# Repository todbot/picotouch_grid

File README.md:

# picotouch_grid

## Demo

https://github.com/user-attachments/assets/54ee2066-7102-474b-aefb-f99e8350b503

another on youtube:  https://www.youtube.com/watch?v=ulmvLfkXsHI

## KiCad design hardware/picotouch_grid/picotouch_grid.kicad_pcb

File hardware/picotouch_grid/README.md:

Uses JLCPCB rules from https://github.com/labtroll/KiCad-DesignRules

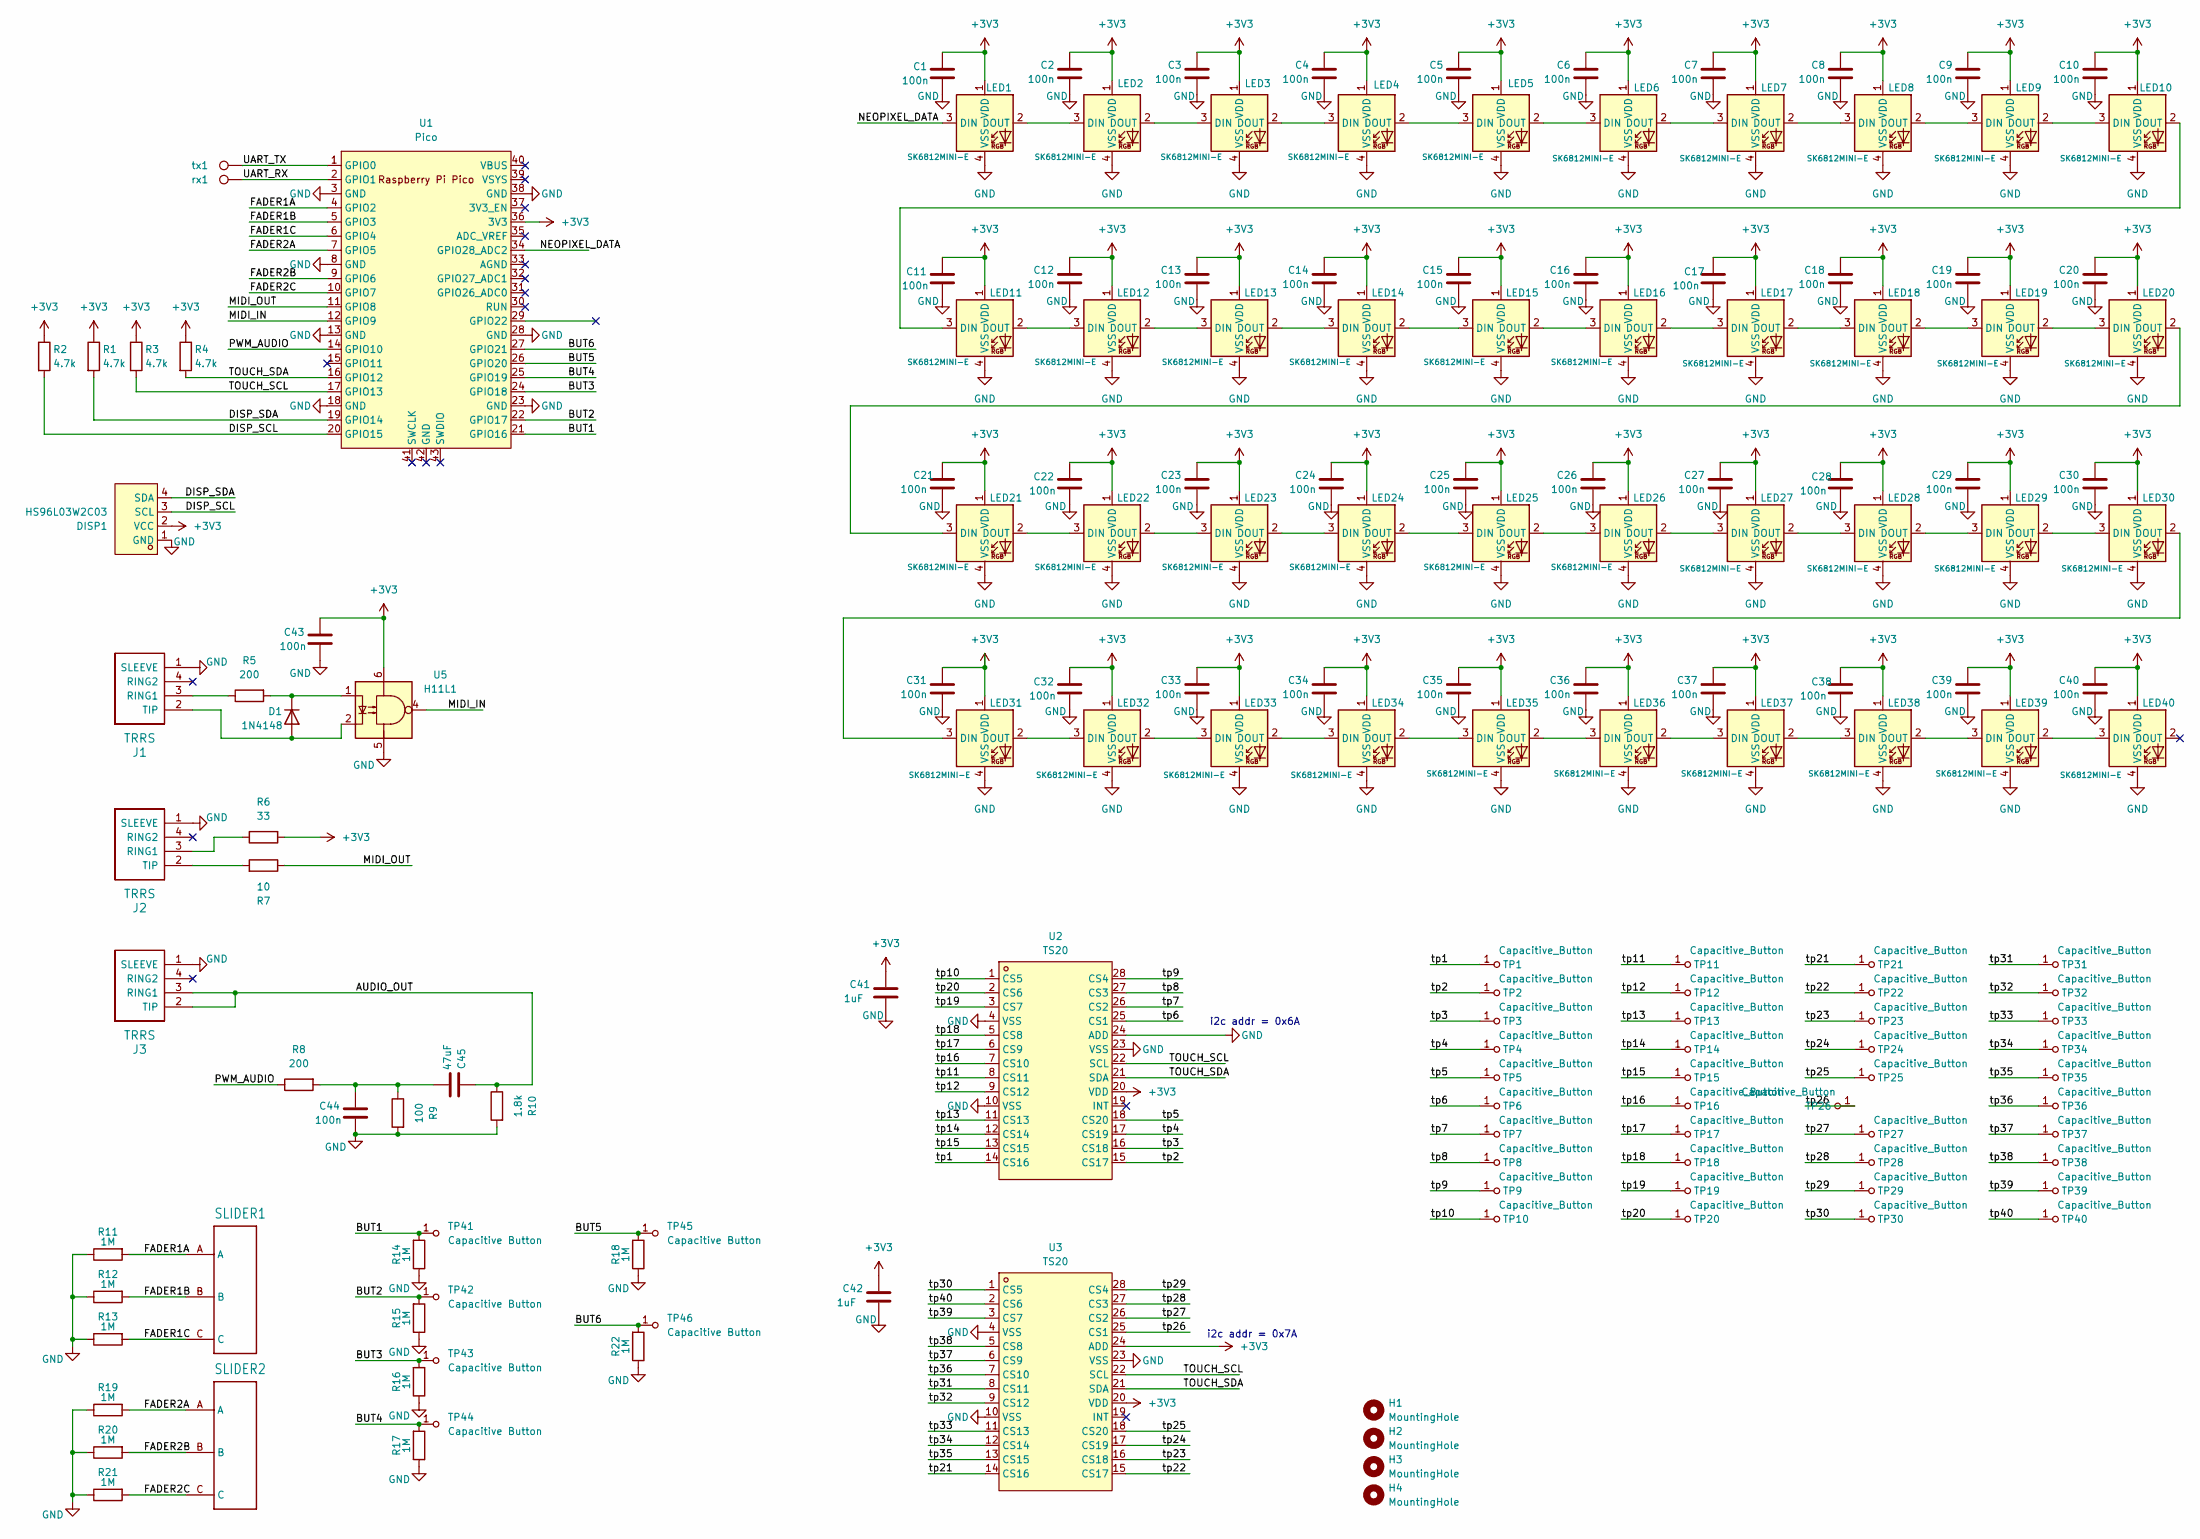
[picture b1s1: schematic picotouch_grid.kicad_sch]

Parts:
C1, C2, C3, C4, C5, C6, C7, C8, C9, C10, C11, C12, C13, C14, C15, C16, C17, C18, C19, C20, C21, C22, C23, C24, C25, C26, C27, C28, C29, C30, C31, C32, C33, C34, C35, C36, C37, C38, C39, C40, C43, C44: 100n; C_0603_1608Metric
C41, C42: 1uF; C_0603_1608Metric
C45: 47uF; C_0603_1608Metric
D1: 1N4148; D_SOD-123
DISP1: HS96L03W2C03; OLED-TH_under_fixed_L27.8-W27.2-P2.54_C9900033791; LCSC Part C5248080
H1, H2, H3, H4: MountingHole; MountingHole_2.7mm_M2.5
J1, J2, J3: TRRS; TRRS-PJ-320D
LED1, LED2, LED3, LED4, LED5, LED6, LED7, LED8, LED9, LED10, LED11, LED12, LED13, LED14, LED15, LED16, LED17, LED18, LED19, LED20, LED21, LED22, LED23, LED24, LED25, LED26, LED27, LED28, LED29, LED30, LED31, LED32, LED33, LED34, LED35, LED36, LED37, LED38, LED39, LED40: SK6812MINI-E; LED_6028R
R1, R2, R3, R4: 4.7k; R_0603_1608Metric
R5, R8: 200; R_0603_1608Metric
R6: 33; R_0603_1608Metric
R7: 10; R_0603_1608Metric
R9: 100; R_0603_1608Metric
R10: 1.8k; R_0603_1608Metric
R11, R12, R13, R14, R15, R16, R17, R18, R19, R20, R21, R22: 1M; R_0603_1608Metric
SLIDER1, SLIDER2: TOUCHSLIDER3_8x40B
TP1, TP2, TP3, TP4, TP5, TP6, TP7, TP8, TP9, TP10, TP11, TP12, TP13, TP14, TP15, TP16, TP17, TP18, TP19, TP20, TP21, TP22, TP23, TP24, TP25, TP26, TP27, TP28, TP29, TP30, TP31, TP32, TP33, TP34, TP35, TP36, TP37, TP38, TP39, TP40: Capacitive_Button; TOUCHPAD_KEY_0.5IN_LEDHOLE
TP41, TP42, TP43, TP44, TP45, TP46: Capacitive Button; Pad-CapacitiveTouch
U1: Pico; RPi_Pico_SMD
U2, U3: TS20; TSSOP-28_L9.7-W4.4-P0.65-LS6.4-BL; LCSC Part C95876
U5: H11L1; DIP-6_W8.89mm_SMDSocket_LongPads
rx1: rx; TestPoint_Pad_D2.0mm
tx1: tx; TestPoint_Pad_D2.0mm

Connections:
+3V3: C1.1, C2.1, C3.1, C4.1, C5.1, C6.1, C7.1, C8.1, C9.1, C10.1, C11.1, C12.1, C13.1, C14.1, C15.1, C16.1, C17.1, C18.1, C19.1, C20.1, C21.1, C22.1, C23.1, C24.1, C25.1, C26.1, C27.1, C28.1, C29.1, C30.1, C31.1, C32.1, C33.1, C34.1, C35.1, C36.1, C37.1, C38.1, C39.1, C40.1, C41.1, C42.1, C43.1, DISP1.2 (VCC), LED1.1 (VDD), LED2.1 (VDD), LED3.1 (VDD), LED4.1 (VDD), LED5.1 (VDD), LED6.1 (VDD), LED7.1 (VDD), LED8.1 (VDD), LED9.1 (VDD), LED10.1 (VDD), LED11.1 (VDD), LED12.1 (VDD), LED13.1 (VDD), LED14.1 (VDD), LED15.1 (VDD), LED16.1 (VDD), LED17.1 (VDD), LED18.1 (VDD), LED19.1 (VDD), LED20.1 (VDD), LED21.1 (VDD), LED22.1 (VDD), LED23.1 (VDD), LED24.1 (VDD), LED25.1 (VDD), LED26.1 (VDD), LED27.1 (VDD), LED28.1 (VDD), LED29.1 (VDD), LED30.1 (VDD), LED31.1 (VDD), LED32.1 (VDD), LED33.1 (VDD), LED34.1 (VDD), LED35.1 (VDD), LED36.1 (VDD), LED37.1 (VDD), LED38.1 (VDD), LED39.1 (VDD), LED40.1 (VDD), R1.1, R2.1, R3.1, R4.1, R6.2, U1.36 (3V3), U2.20 (VDD), U3.20 (VDD), U3.24 (ADD), U5.6
/AUDIO_OUT: C45.1, J3.2 (TIP), J3.3 (RING1), R10.1
/BUT1: R14.2, TP41.1 (A), U1.21 (GPIO16)
/BUT2: R15.2, TP42.1 (A), U1.22 (GPIO17)
/BUT3: R16.2, TP43.1 (A), U1.24 (GPIO18)
/BUT4: R17.2, TP44.1 (A), U1.25 (GPIO19)
/BUT5: R18.2, TP45.1 (A), U1.26 (GPIO20)
/BUT6: R22.2, TP46.1 (A), U1.27 (GPIO21)
/DISP_SCL: DISP1.3 (SCL), R2.2, U1.20 (GPIO15)
/DISP_SDA: DISP1.4 (SDA), R1.2, U1.19 (GPIO14)
/FADER1A: R11.2, SLIDER1.A, U1.4 (GPIO2)
/FADER1B: R12.2, SLIDER1.B, U1.5 (GPIO3)
/FADER1C: R13.2, SLIDER1.C, U1.6 (GPIO4)
/FADER2A: R19.2, SLIDER2.A, U1.7 (GPIO5)
/FADER2B: R20.2, SLIDER2.B, U1.9 (GPIO6)
/FADER2C: R21.2, SLIDER2.C, U1.10 (GPIO7)
/MIDI_IN: U1.12 (GPIO9), U5.4
/MIDI_OUT: R7.1, U1.11 (GPIO8)
/NEOPIXEL_DATA: LED1.3 (DIN), U1.34 (GPIO28_ADC2)
/PWM_AUDIO: R8.1, U1.14 (GPIO10)
/TOUCH_SCL: R3.2, U1.17 (GPIO13), U2.22 (SCL), U3.22 (SCL)
/TOUCH_SDA: R4.2, U1.16 (GPIO12), U2.21 (SDA), U3.21 (SDA)
/UART_RX: U1.2 (GPIO1), rx1.1
/UART_TX: U1.1 (GPIO0), tx1.1
/tp1: TP1.1 (A), U2.14 (CS16)
/tp2: TP2.1 (A), U2.15 (CS17)
/tp3: TP3.1 (A), U2.16 (CS18)
/tp4: TP4.1 (A), U2.17 (CS19)
/tp5: TP5.1 (A), U2.18 (CS20)
/tp6: TP6.1 (A), U2.25 (CS1)
/tp7: TP7.1 (A), U2.26 (CS2)
/tp8: TP8.1 (A), U2.27 (CS3)
/tp9: TP9.1 (A), U2.28 (CS4)
/tp10: TP10.1 (A), U2.1 (CS5)
/tp11: TP11.1 (A), U2.8 (CS11)
/tp12: TP12.1 (A), U2.9 (CS12)
/tp13: TP13.1 (A), U2.11 (CS13)
/tp14: TP14.1 (A), U2.12 (CS14)
/tp15: TP15.1 (A), U2.13 (CS15)
/tp16: TP16.1 (A), U2.7 (CS10)
/tp17: TP17.1 (A), U2.6 (CS9)
/tp18: TP18.1 (A), U2.5 (CS8)
/tp19: TP19.1 (A), U2.3 (CS7)
/tp20: TP20.1 (A), U2.2 (CS6)
/tp21: TP21.1 (A), U3.14 (CS16)
/tp22: TP22.1 (A), U3.15 (CS17)
/tp23: TP23.1 (A), U3.16 (CS18)
/tp24: TP24.1 (A), U3.17 (CS19)
/tp25: TP25.1 (A), U3.18 (CS20)
/tp26: TP26.1 (A), U3.25 (CS1)
/tp27: TP27.1 (A), U3.26 (CS2)
/tp28: TP28.1 (A), U3.27 (CS3)
/tp29: TP29.1 (A), U3.28 (CS4)
/tp30: TP30.1 (A), U3.1 (CS5)
/tp31: TP31.1 (A), U3.8 (CS11)
/tp32: TP32.1 (A), U3.9 (CS12)
/tp33: TP33.1 (A), U3.11 (CS13)
/tp34: TP34.1 (A), U3.12 (CS14)
/tp35: TP35.1 (A), U3.13 (CS15)
/tp36: TP36.1 (A), U3.7 (CS10)
/tp37: TP37.1 (A), U3.6 (CS9)
/tp38: TP38.1 (A), U3.5 (CS8)
/tp39: TP39.1 (A), U3.3 (CS7)
/tp40: TP40.1 (A), U3.2 (CS6)
GND: C1.2, C2.2, C3.2, C4.2, C5.2, C6.2, C7.2, C8.2, C9.2, C10.2, C11.2, C12.2, C13.2, C14.2, C15.2, C16.2, C17.2, C18.2, C19.2, C20.2, C21.2, C22.2, C23.2, C24.2, C25.2, C26.2, C27.2, C28.2, C29.2, C30.2, C31.2, C32.2, C33.2, C34.2, C35.2, C36.2, C37.2, C38.2, C39.2, C40.2, C41.2, C42.2, C43.2, C44.2, DISP1.1 (GND), J1.1 (SLEEVE), J2.1 (SLEEVE), J3.1 (SLEEVE), LED1.4 (VSS), LED2.4 (VSS), LED3.4 (VSS), LED4.4 (VSS), LED5.4 (VSS), LED6.4 (VSS), LED7.4 (VSS), LED8.4 (VSS), LED9.4 (VSS), LED10.4 (VSS), LED11.4 (VSS), LED12.4 (VSS), LED13.4 (VSS), LED14.4 (VSS), LED15.4 (VSS), LED16.4 (VSS), LED17.4 (VSS), LED18.4 (VSS), LED19.4 (VSS), LED20.4 (VSS), LED21.4 (VSS), LED22.4 (VSS), LED23.4 (VSS), LED24.4 (VSS), LED25.4 (VSS), LED26.4 (VSS), LED27.4 (VSS), LED28.4 (VSS), LED29.4 (VSS), LED30.4 (VSS), LED31.4 (VSS), LED32.4 (VSS), LED33.4 (VSS), LED34.4 (VSS), LED35.4 (VSS), LED36.4 (VSS), LED37.4 (VSS), LED38.4 (VSS), LED39.4 (VSS), LED40.4 (VSS), R9.2, R10.2, R11.1, R12.1, R13.1, R14.1, R15.1, R16.1, R17.1, R18.1, R19.1, R20.1, R21.1, R22.1, U1.3 (GND), U1.8 (GND), U1.13 (GND), U1.18 (GND), U1.23 (GND), U1.28 (GND), U1.38 (GND), U2.4 (VSS), U2.10 (VSS), U2.23 (VSS), U2.24 (ADD), U3.4 (VSS), U3.10 (VSS), U3.23 (VSS), U5.5
unnamed: C44.1, C45.2, R8.2, R9.1
unnamed: D1.2 (A), J1.2 (TIP), U5.2
unnamed: D1.1 (K), R5.2, U5.1
unnamed: J1.3 (RING1), R5.1
unnamed: J2.3 (RING1), R6.1
unnamed: J2.2 (TIP), R7.2
unnamed: LED1.2 (DOUT), LED2.3 (DIN)
unnamed: LED2.2 (DOUT), LED3.3 (DIN)
unnamed: LED3.2 (DOUT), LED4.3 (DIN)
unnamed: LED4.2 (DOUT), LED5.3 (DIN)
unnamed: LED5.2 (DOUT), LED6.3 (DIN)
unnamed: LED6.2 (DOUT), LED7.3 (DIN)
unnamed: LED7.2 (DOUT), LED8.3 (DIN)
unnamed: LED8.2 (DOUT), LED9.3 (DIN)
unnamed: LED9.2 (DOUT), LED10.3 (DIN)
unnamed: LED10.2 (DOUT), LED11.3 (DIN)
unnamed: LED11.2 (DOUT), LED12.3 (DIN)
unnamed: LED12.2 (DOUT), LED13.3 (DIN)
unnamed: LED13.2 (DOUT), LED14.3 (DIN)
unnamed: LED14.2 (DOUT), LED15.3 (DIN)
unnamed: LED15.2 (DOUT), LED16.3 (DIN)
unnamed: LED16.2 (DOUT), LED17.3 (DIN)
unnamed: LED17.2 (DOUT), LED18.3 (DIN)
unnamed: LED18.2 (DOUT), LED19.3 (DIN)
unnamed: LED19.2 (DOUT), LED20.3 (DIN)
unnamed: LED20.2 (DOUT), LED21.3 (DIN)
unnamed: LED21.2 (DOUT), LED22.3 (DIN)
unnamed: LED22.2 (DOUT), LED23.3 (DIN)
unnamed: LED23.2 (DOUT), LED24.3 (DIN)
unnamed: LED24.2 (DOUT), LED25.3 (DIN)
unnamed: LED25.2 (DOUT), LED26.3 (DIN)
unnamed: LED26.2 (DOUT), LED27.3 (DIN)
unnamed: LED27.2 (DOUT), LED28.3 (DIN)
unnamed: LED28.2 (DOUT), LED29.3 (DIN)
unnamed: LED29.2 (DOUT), LED30.3 (DIN)
unnamed: LED30.2 (DOUT), LED31.3 (DIN)
unnamed: LED31.2 (DOUT), LED32.3 (DIN)
unnamed: LED32.2 (DOUT), LED33.3 (DIN)
unnamed: LED33.2 (DOUT), LED34.3 (DIN)
unnamed: LED34.2 (DOUT), LED35.3 (DIN)
unnamed: LED35.2 (DOUT), LED36.3 (DIN)
unnamed: LED36.2 (DOUT), LED37.3 (DIN)
unnamed: LED37.2 (DOUT), LED38.3 (DIN)
unnamed: LED38.2 (DOUT), LED39.3 (DIN)
unnamed: LED39.2 (DOUT), LED40.3 (DIN)

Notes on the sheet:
i2c addr = 0x7A
i2c addr = 0x6A

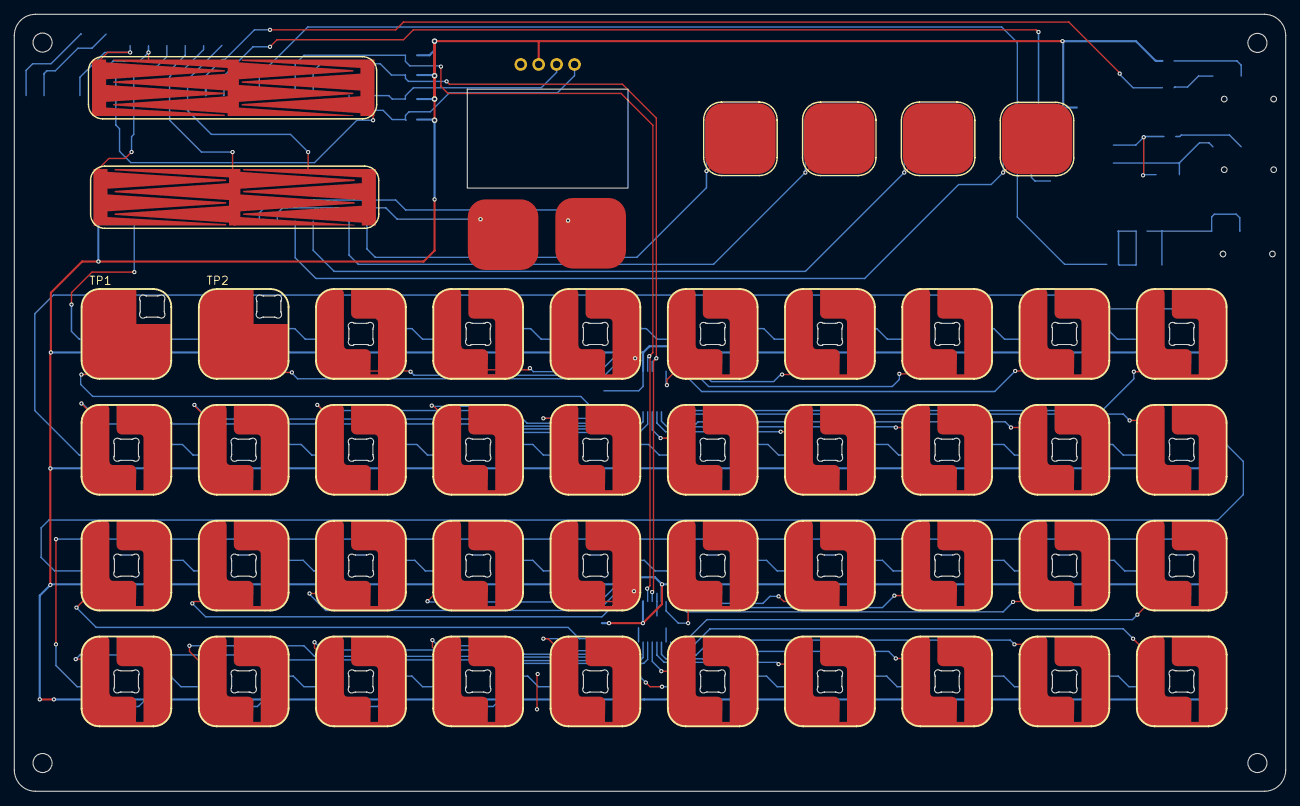
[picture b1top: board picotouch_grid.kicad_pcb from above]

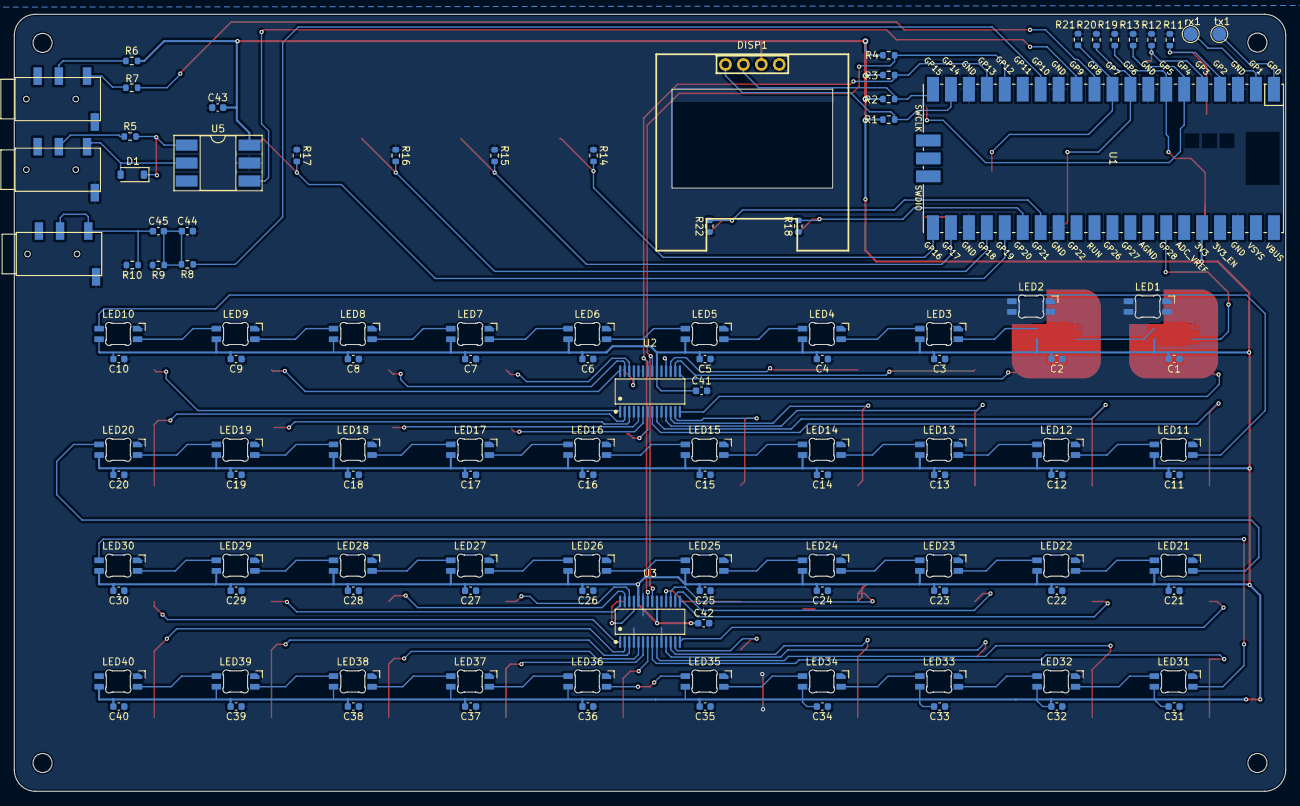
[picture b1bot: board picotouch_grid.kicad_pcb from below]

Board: 2 copper layers, 180.0 x 110.0 mm, 170 parts (117 on the bottom side), 110 nets.

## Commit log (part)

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2024-03-18 made some pcb progress from old picotouch_grid_mpr board in Eagle in picotouch repo
2024-03-19 more pcb routing done
2024-03-19 pads mostly routed
2024-03-19 pcb captouch routing passes DRC
2024-03-19 pcb DRC, with footprints updated (why was this needed)
2024-03-19 added jlcpcb dru rules from "KiCad-DesignRules"
2024-03-20 pcb: added midi in/out, pwm audio out
2024-03-20 pcb: add more buttons, clean up layout of sch & pcb
2024-03-21 pcb: tune button layout
2024-03-21 pcb: another fader, i2c trace reorg
2024-03-22 pcb: button layout tune
2024-04-23 getting back into this, updated some stuff, getting lots of ERC, got some power pins wrong?
2024-11-05 add picotouch_grid_mpr reseach code for cooper to peak at
